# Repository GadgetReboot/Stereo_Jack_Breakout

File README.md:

# Stereo_Jack_Breakout
Dual stacking 1/4" stereo jack breakout pcb for 2x5 stereo switched jacks to 0.1 inch headers 

<BR>Jack:  Neutrik NSJ12HF-1  https://www.mouser.ca/ProductDetail/568-NSJ12HF-1
<BR>Datasheet:  https://www.mouser.ca/datasheet/2/289/nsj12hf-1-3-1853820.pdf

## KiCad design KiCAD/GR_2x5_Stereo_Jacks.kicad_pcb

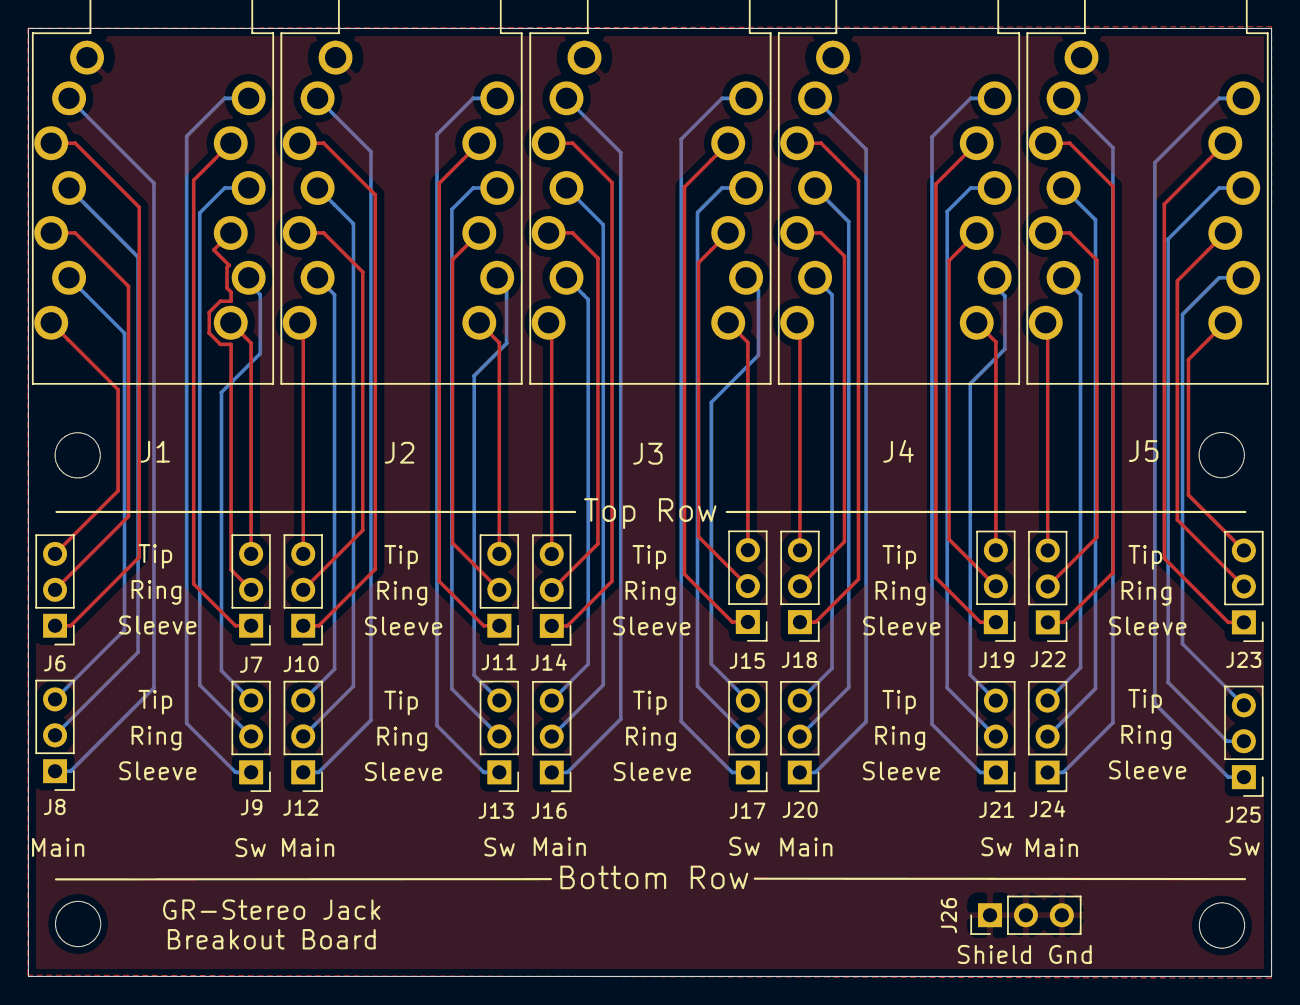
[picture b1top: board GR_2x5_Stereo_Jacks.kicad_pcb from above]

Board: 2 copper layers, 87.9 x 67.0 mm, 30 parts (0 on the bottom side), 61 nets.

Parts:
J1, J2, J3, J4, J5: NSJ12HF-1; Phone_Stereo_Stacking_NSJ12HF-1
J6, J7, J8, J9, J10, J11, J12, J13, J14, J15, J16, J17, J18, J19, J20, J21, J22, J23, J24, J25, J26: Conn_01x03; PinHeader_1x03_P2.54mm_Vertical
MH1, MH2, MH3, MH4: MountingHole; MountingHole_3.2mm_M3

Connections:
/Ring_Bot_1: J1.R_BOT, J8.2
/Ring_Bot_2: J2.R_BOT, J12.2
/Ring_Bot_3: J3.R_BOT, J16.2
/Ring_Bot_4: J4.R_BOT, J20.2
/Ring_Bot_5: J5.R_BOT, J24.2
/Ring_Sw_Bot_1: J1.R_SW_BOT, J9.2
/Ring_Sw_Bot_2: J2.R_SW_BOT, J13.2
/Ring_Sw_Bot_3: J3.R_SW_BOT, J17.2
/Ring_Sw_Bot_4: J4.R_SW_BOT, J21.2
/Ring_Sw_Bot_5: J5.R_SW_BOT, J25.2
/Ring_Sw_Top_1: J1.R_SW_TOP, J7.2
/Ring_Sw_Top_2: J2.R_SW_TOP, J11.2
/Ring_Sw_Top_3: J3.R_SW_TOP, J15.2
/Ring_Sw_Top_4: J4.R_SW_TOP, J19.2
/Ring_Sw_Top_5: J5.R_SW_TOP, J23.2
/Ring_Top_1: J1.R_TOP, J6.2
/Ring_Top_2: J2.R_TOP, J10.2
/Ring_Top_3: J3.R_TOP, J14.2
/Ring_Top_4: J4.R_TOP, J18.2
/Ring_Top_5: J5.R_TOP, J22.2
/Sleeve_Bot_1: J1.S_BOT, J8.1
/Sleeve_Bot_2: J2.S_BOT, J12.1
/Sleeve_Bot_3: J3.S_BOT, J16.1
/Sleeve_Bot_4: J4.S_BOT, J20.1
/Sleeve_Bot_5: J5.S_BOT, J24.1
/Sleeve_Sw_Bot_1: J1.S_SW_BOT, J9.1
/Sleeve_Sw_Bot_2: J2.S_SW_BOT, J13.1
/Sleeve_Sw_Bot_3: J3.S_SW_BOT, J17.1
/Sleeve_Sw_Bot_4: J4.S_SW_BOT, J21.1
/Sleeve_Sw_Bot_5: J5.S_SW_BOT, J25.1
/Sleeve_Sw_Top_1: J1.S_SW_TOP, J7.1
/Sleeve_Sw_Top_2: J2.S_SW_TOP, J11.1
/Sleeve_Sw_Top_3: J3.S_SW_TOP, J15.1
/Sleeve_Sw_Top_4: J4.S_SW_TOP, J19.1
/Sleeve_Sw_Top_5: J5.S_SW_TOP, J23.1
/Sleeve_Top_1: J1.S_TOP, J6.1
/Sleeve_Top_2: J2.S_TOP, J10.1
/Sleeve_Top_3: J3.S_TOP, J14.1
/Sleeve_Top_4: J4.S_TOP, J18.1
/Sleeve_Top_5: J5.S_TOP, J22.1
/Tip_Bot_1: J1.T_BOT, J8.3
/Tip_Bot_2: J2.T_BOT, J12.3
/Tip_Bot_3: J3.T_BOT, J16.3
/Tip_Bot_4: J4.T_BOT, J20.3
/Tip_Bot_5: J5.T_BOT, J24.3
/Tip_Sw_Bot_1: J1.T_SW_BOT, J9.3
/Tip_Sw_Bot_2: J2.T_SW_BOT, J13.3
/Tip_Sw_Bot_3: J3.T_SW_BOT, J17.3
/Tip_Sw_Bot_4: J4.T_SW_BOT, J21.3
/Tip_Sw_Bot_5: J5.T_SW_BOT, J25.3
/Tip_Sw_Top_1: J1.T_SW_TOP, J7.3
/Tip_Sw_Top_2: J2.T_SW_TOP, J11.3
/Tip_Sw_Top_3: J3.T_SW_TOP, J15.3
/Tip_Sw_Top_4: J4.T_SW_TOP, J19.3
/Tip_Sw_Top_5: J5.T_SW_TOP, J23.3
/Tip_Top_1: J1.T_TOP, J6.3
/Tip_Top_2: J2.T_TOP, J10.3
/Tip_Top_3: J3.T_TOP, J14.3
/Tip_Top_4: J4.T_TOP, J18.3
/Tip_Top_5: J5.T_TOP, J22.3
GNDREF: J1.Shield, J2.Shield, J3.Shield, J4.Shield, J5.Shield, J26.1, J26.2, J26.3
